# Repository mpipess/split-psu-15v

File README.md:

# split-psu-15v

## Concept

This is a basic split-rail power supply to support my analog projects.
It's also my first power-related project, so a learning experience.
Thankfully the datasheet for the main PMIC is quite nice to follow.
That PMIC being the TPS65131 from TI.

## Status

Have the boards and parts. Trying to find time to assemble.

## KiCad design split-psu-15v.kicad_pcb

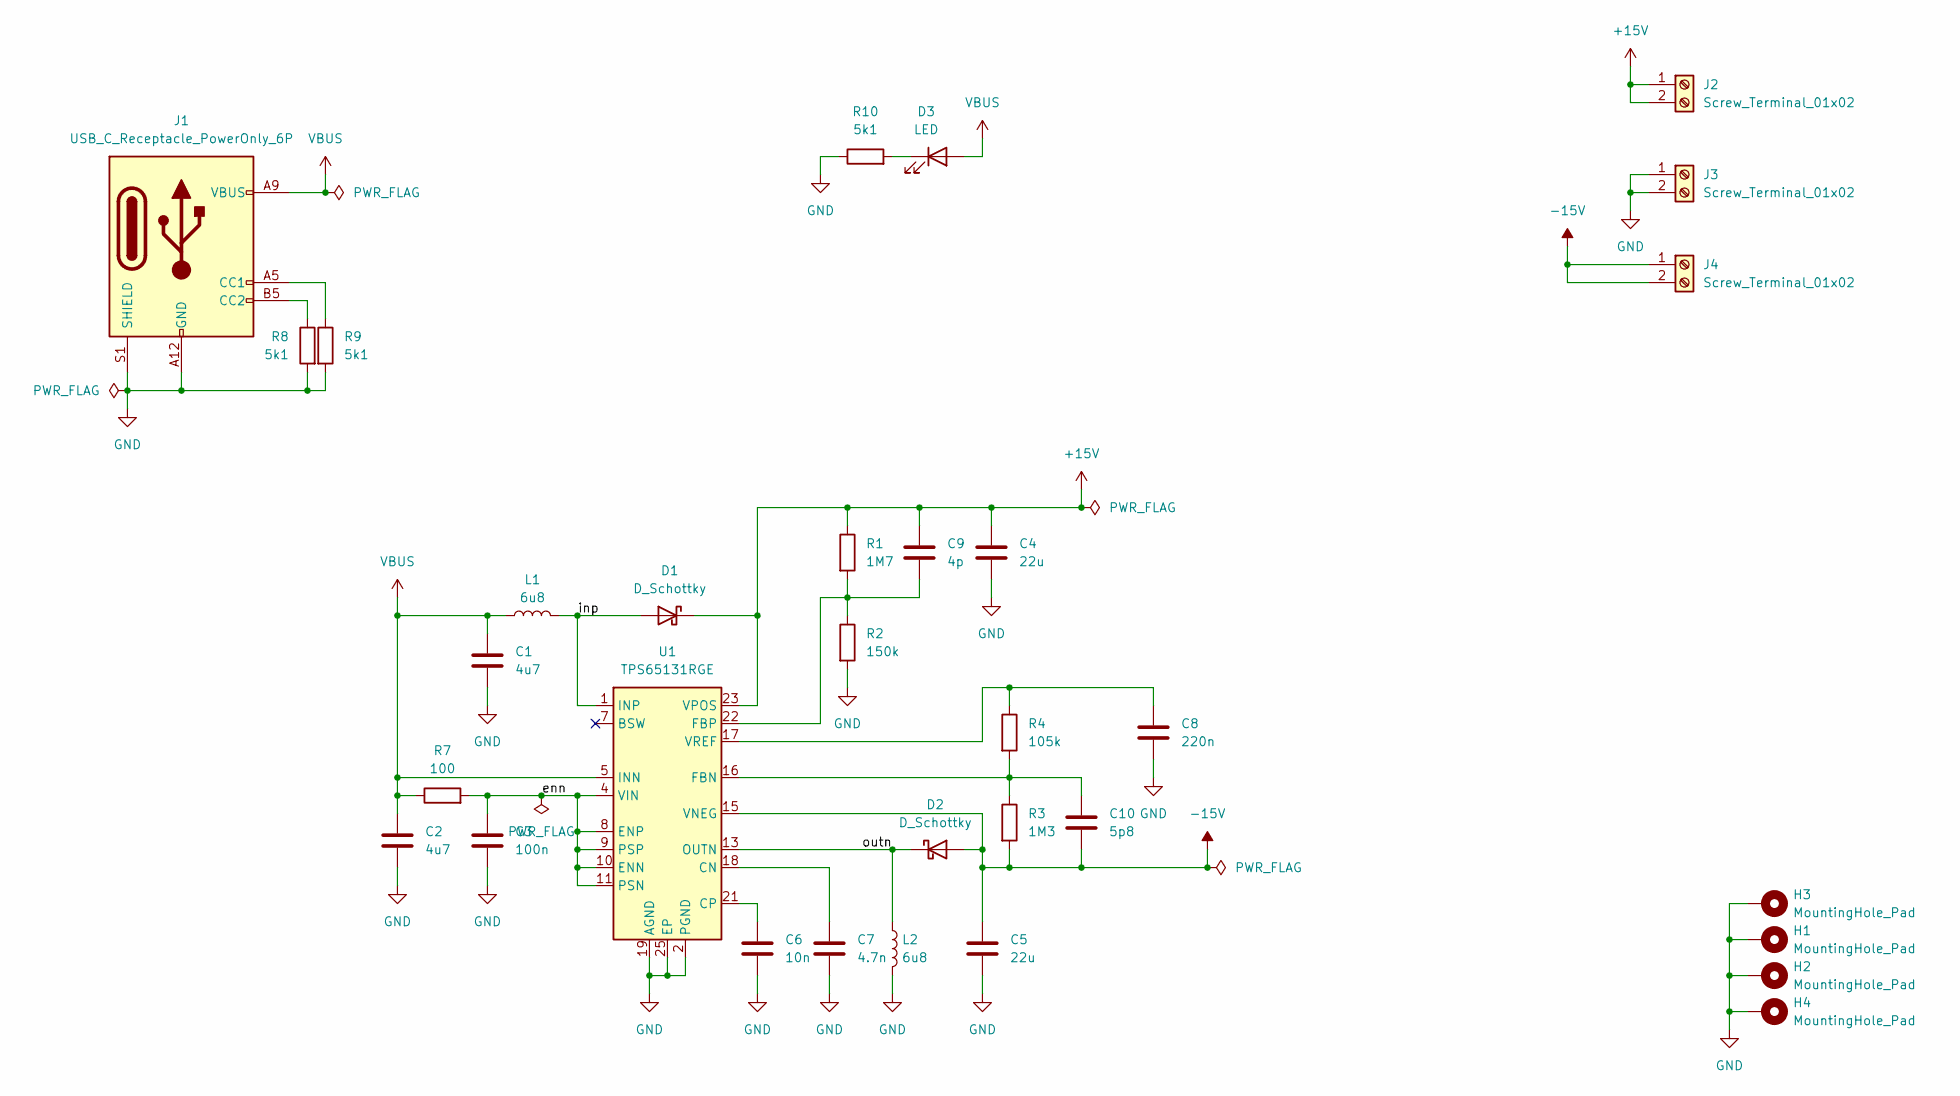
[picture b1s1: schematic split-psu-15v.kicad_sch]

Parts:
C1, C2: 4u7; C_0805_2012Metric
C3: 100n; C_0603_1608Metric
C4, C5: 22u; C_0805_2012Metric
C6: 10n; C_0603_1608Metric
C7: 4.7n; C_0603_1608Metric
C8: 220n; C_0603_1608Metric
C9: 4p; C_0603_1608Metric
C10: 5p8; C_0603_1608Metric
D1, D2: D_Schottky; D_SMP_DO-220AA
D3: LED; LED_0805_2012Metric
H1, H2, H3, H4: MountingHole_Pad; MountingHole_2.2mm_M2_DIN965_Pad_TopBottom
J1: USB_C_Receptacle_PowerOnly_6P; USB_C_Receptacle_GCT_USB4125-xx-x_6P_TopMnt_Horizontal
J2, J3, J4: Screw_Terminal_01x02; TerminalBlock_Phoenix_MKDS-1,5-2-5.08_1x02_P5.08mm_Horizont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
L1, L2: 6u8; L_Taiyo-Yuden_MD-5050
R1: 1M7; R_0603_1608Metric
R2: 150k; R_0603_1608Metric
R3: 1M3; R_0603_1608Metric
R4: 105k; R_0603_1608Metric
R7: 100; R_0603_1608Metric
R8, R9, R10: 5k1; R_0805_2012Metric
U1: TPS65131RGE; VQFN-24-1EP_4x4mm_P0.5mm_EP2.45x2.45mm_ThermalVias

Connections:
+15V: C4.1, C9.1, D1.1 (K), J2.1, J2.2, R1.1, U1.23 (VPOS)
-15V: C5.1, C10.2, D2.2 (A), J4.1, J4.2, R3.2, U1.15 (VNEG)
/enn: C3.1, R7.2, U1.4 (VIN), U1.8 (ENP), U1.9 (PSP), U1.10 (ENN), U1.11 (PSN)
/inp: D1.2 (A), L1.2, U1.1 (INP), U1.24 (INP)
/outn: D2.1 (K), L2.1, U1.13 (OUTN), U1.14 (OUTN)
GND: C1.2, C2.2, C3.2, C4.2, C5.2, C6.2, C7.2, C8.2, H1.1, H2.1, H3.1, H4.1, J1.A12 (GND), J1.B12 (GND), J1.S1 (SHIELD), J3.1, J3.2, L2.2, R2.2, R8.2, R9.2, R10.1, U1.2 (PGND), U1.3 (PGND), U1.19 (AGND), U1.25 (EP)
unnamed: D3.1 (K), R10.2
unnamed: J1.A5 (CC1), R9.1
unnamed: J1.B5 (CC2), R8.1
unnamed: C7.1, U1.18 (CN)
unnamed: C6.1, U1.21 (CP)
unnamed: C10.1, R3.1, R4.2, U1.16 (FBN)
unnamed: C9.2, R1.2, R2.1, U1.22 (FBP)
unnamed: C8.1, R4.1, U1.17 (VREF)
VBUS: C1.1, C2.1, D3.2 (A), J1.A9 (VBUS), J1.B9 (VBUS), L1.1, R7.1, U1.5 (INN), U1.6 (INN)

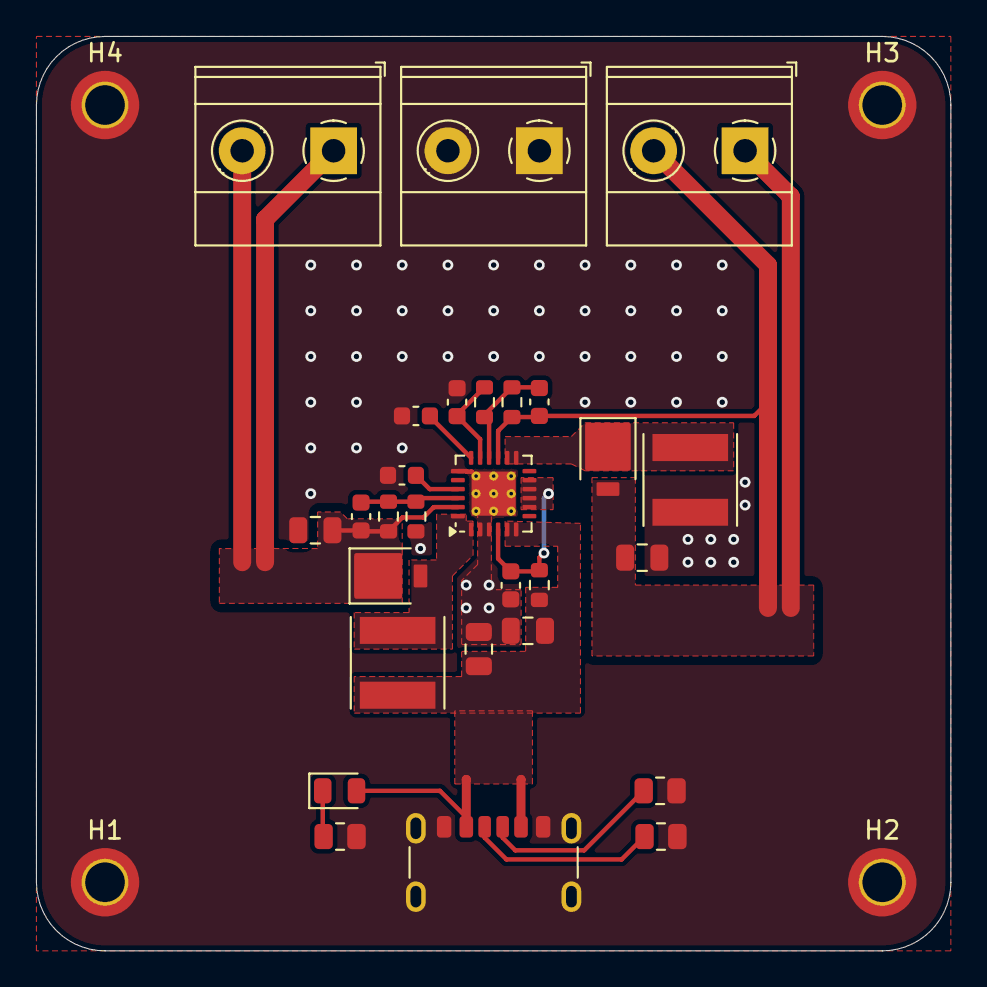
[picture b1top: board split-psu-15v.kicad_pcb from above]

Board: 2 copper layers, 50.8 x 50.8 mm, 32 parts (0 on the bottom side), 15 nets.

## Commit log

2024-09-28 add README
2024-10-28 update project status
